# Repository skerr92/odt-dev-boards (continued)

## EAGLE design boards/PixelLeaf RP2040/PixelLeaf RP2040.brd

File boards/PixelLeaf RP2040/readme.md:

# PixelLeaf RP2040 Design Files

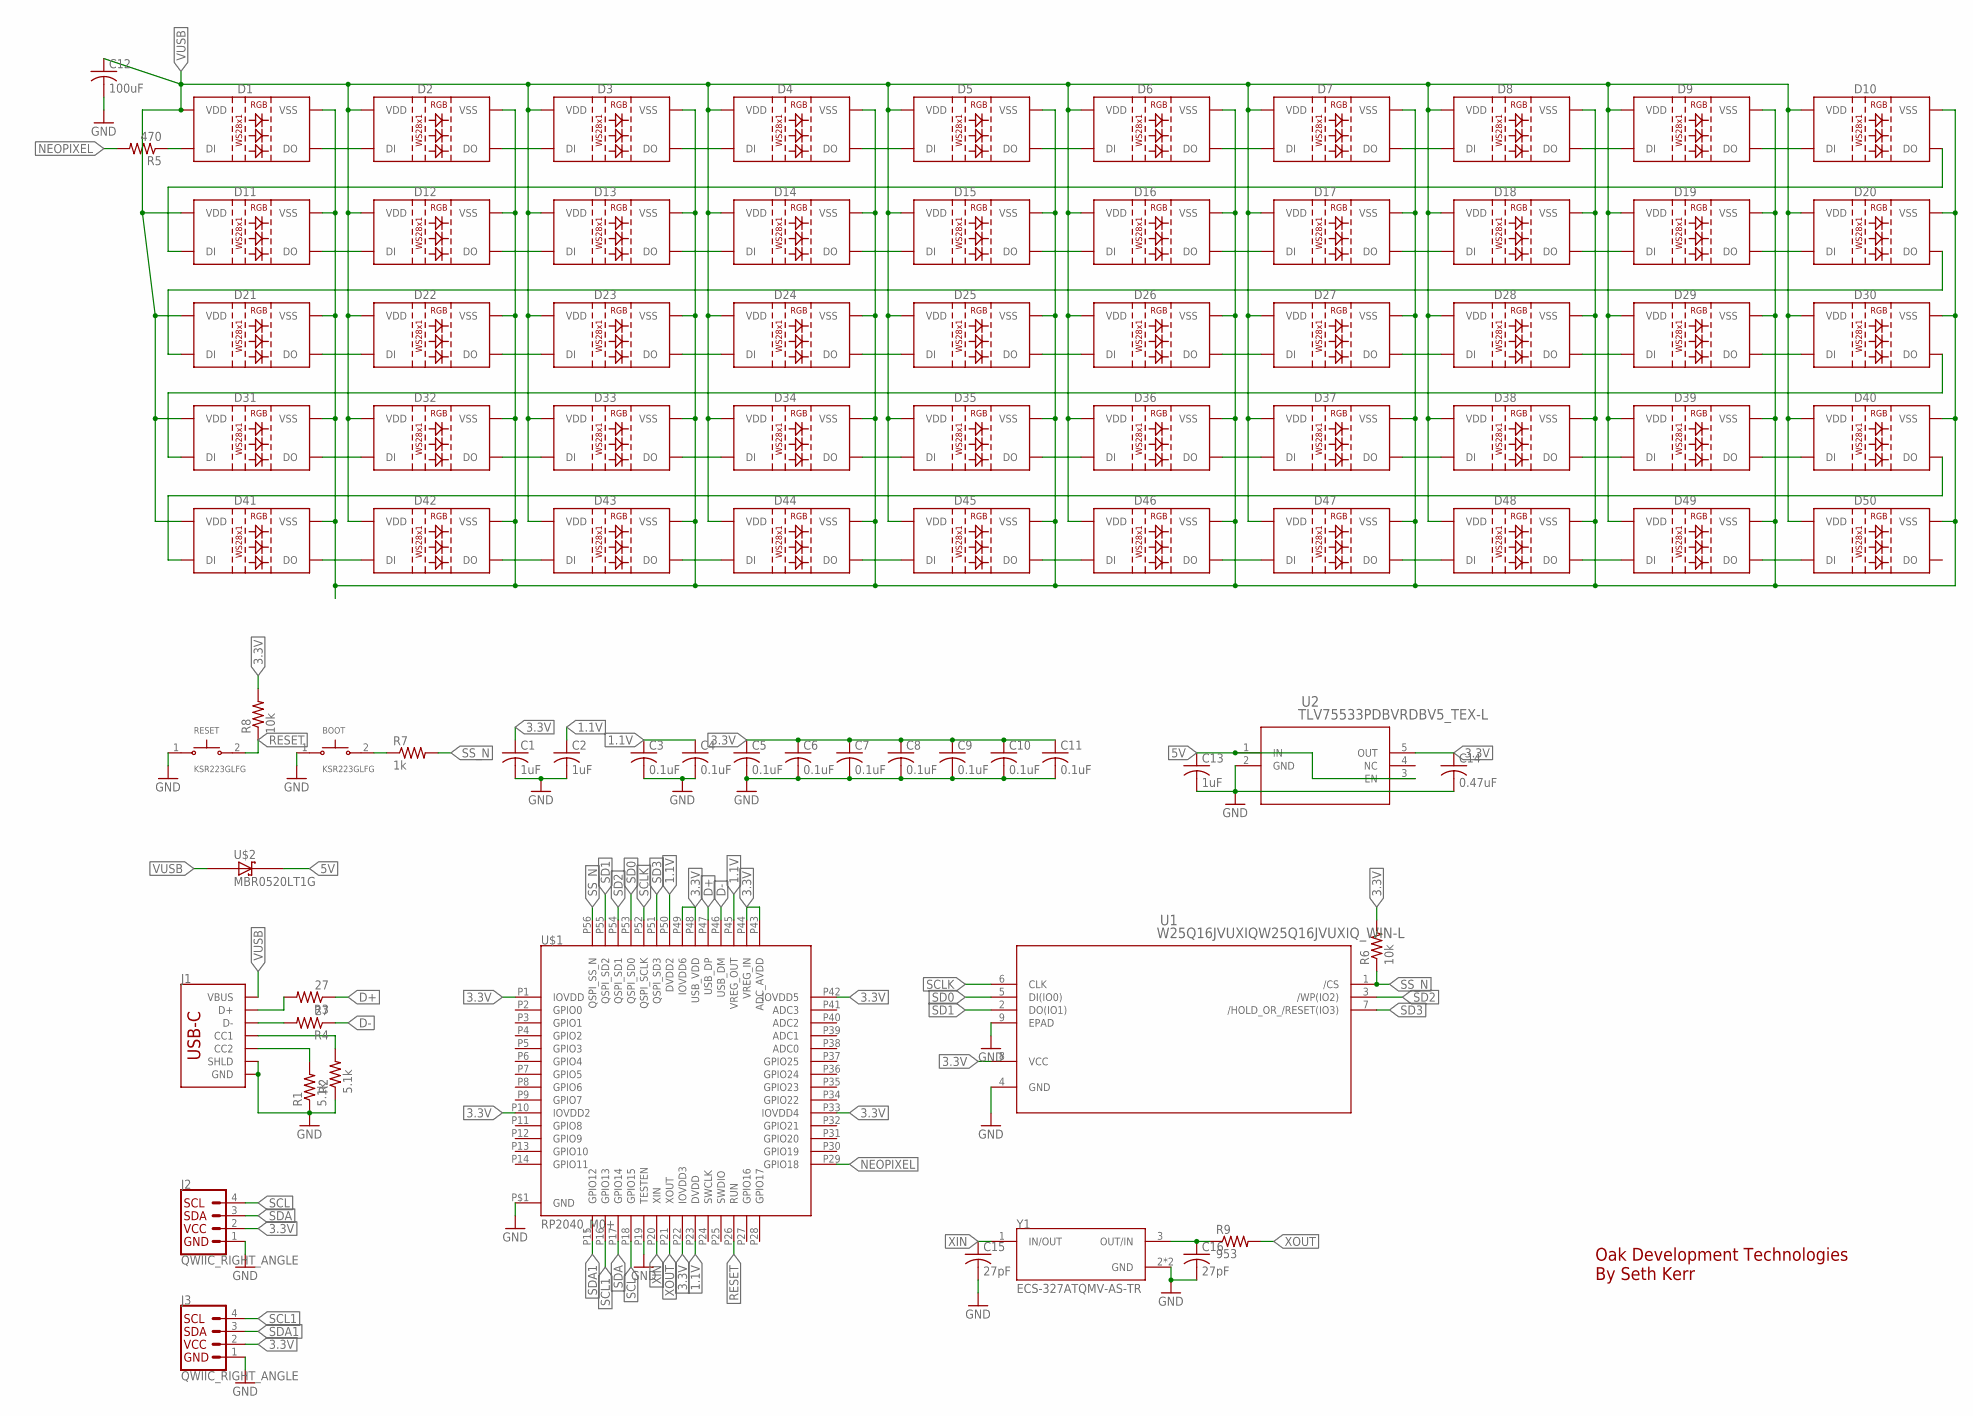
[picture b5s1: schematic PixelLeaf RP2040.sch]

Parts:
BOOT: KSR223GLFG; SW_KSR223GLFG
C1, C2, C13: 1uF; C0603
C3, C4, C5, C6, C7, C8, C9, C10, C11: 0.1uF; C0603
C12: 100uF; C1206
C14: 0.47uF; C0603
C15, C16: 27pF; C0402
D1, D2, D3, D4, D5, D6, D7, D8, D9, D10, D11, D12, D13, D14, D15, D16, D17, D18, D19, D20, D21, D22, D23, D24, D25, D26, D27, D28, D29, D30, D31, D32, D33, D34, D35, D36, D37, D38, D39, D40, D41, D42, D43, D44, D45, D46, D47, D48, D49, D50: WS2812BWS2812B-3535; WS2812-3535
J1: USB_C_2-LAYER_PADS; USB-C-16P-2LAYER-PADS
J2, J3: QWIIC_RIGHT_ANGLE; JST04_1MM_RA
R1, R2: 5.1k; R0603
R3, R4: 27; R0603
R5: 470; R0603
R6, R8: 10k; R0603
R7: 1k; R0603
R9: 953; R0402
RESET: KSR223GLFG; SW_KSR223GLFG
U1: W25Q16JVUXIQW25Q16JVUXIQ_WIN-L; W25Q16JVUXIQ_WIN-L
U2: TLV75533PDBVRDBV5_TEX-L; DBV5_TEX-L
U$1: RP2040_M0+; QFN-56
U$2: MBR0520LT1G; SOD3716X117(SOD-123)
Y1: ECS-327ATQMV-AS-TR; XTAL_ECS-327ATQMV-AS-TR

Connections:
1.1V: C2.1, C3.1, C4.1, U$1.P23 (DVDD), U$1.P45 (VREG_OUT), U$1.P50 (DVDD2)
3.3V: C1.1, C5.1, C6.1, C7.1, C8.1, C9.1, C10.1, C11.1, C14.1, J2.2, J3.2, R6.2, R8.2, U1.8 (VCC), U2.5 (OUT), U$1.P1 (IOVDD), U$1.P10 (IOVDD2), U$1.P22 (IOVDD3), U$1.P33 (IOVDD4), U$1.P42 (IOVDD5), U$1.P43 (ADC_AVDD), U$1.P44 (VREG_IN), U$1.P48 (USB_VDD), U$1.P49 (IOVDD6)
5V: C13.1, U2.1 (IN), U2.3 (EN), U$2.1 (C)
D+: R3.1, U$1.P47 (USB_DP)
D-: R4.1, U$1.P46 (USB_DM)
GND: BOOT.1, C1.2, C2.2, C3.2, C4.2, C5.2, C6.2, C7.2, C8.2, C9.2, C10.2, C11.2, C12.2, C13.2, C14.2, C15.2, C16.2, D1.VSS, D2.VSS, D3.VSS, D4.VSS, D5.VSS, D6.VSS, D7.VSS, D8.VSS, D9.VSS, D10.VSS, D11.VSS, D12.VSS, D13.VSS, D14.VSS, D15.VSS, D16.VSS, D17.VSS, D18.VSS, D19.VSS, D20.VSS, D21.VSS, D22.VSS, D23.VSS, D24.VSS, D25.VSS, D26.VSS, D27.VSS, D28.VSS, D29.VSS, D30.VSS, D31.VSS, D32.VSS, D33.VSS, D34.VSS, D35.VSS, D36.VSS, D37.VSS, D38.VSS, D39.VSS, D40.VSS, D41.VSS, D42.VSS, D43.VSS, D44.VSS, D45.VSS, D46.VSS, D47.VSS, D48.VSS, D49.VSS, D50.VSS, J1.GND, J1.GND2 (GND), J1.P$1 (SHLD), J1.P$2 (SHLD), J1.P$3 (SHLD), J1.P$4 (SHLD), J1.SHLD1 (SHLD), J1.SHLD2 (SHLD), J1.SHLD3 (SHLD), J1.SHLD4 (SHLD), J2.1, J3.1, R1.1, R2.1, RESET.1, U1.4 (GND), U1.9 (EPAD), U2.2 (GND), U$1.P19 (TESTEN), U$1.P$1 (GND), Y1.2 (GND), Y1.4 (GND)
unnamed: J1.A6 (D+), J1.B6 (D+), R3.2
unnamed: J1.A7 (D-), J1.B7 (D-), R4.2
unnamed: J1.A5 (CC1), R2.2
unnamed: J1.B5 (CC2), R1.2
unnamed: D1.DIN (DI), R5.1
unnamed: C16.1, R9.1, Y1.3 (OUT/IN)
unnamed: D41.DOUT (DO), D42.DIN (DI)
unnamed: D42.DOUT (DO), D43.DIN (DI)
unnamed: D43.DOUT (DO), D44.DIN (DI)
unnamed: D44.DOUT (DO), D45.DIN (DI)
unnamed: D45.DOUT (DO), D46.DIN (DI)
unnamed: D46.DOUT (DO), D47.DIN (DI)
unnamed: D47.DOUT (DO), D48.DIN (DI)
unnamed: D48.DOUT (DO), D49.DIN (DI)
unnamed: D49.DOUT (DO), D50.DIN (DI)
unnamed: D40.DOUT (DO), D41.DIN (DI)
unnamed: D31.DOUT (DO), D32.DIN (DI)
unnamed: D32.DOUT (DO), D33.DIN (DI)
unnamed: D33.DOUT (DO), D34.DIN (DI)
unnamed: D34.DOUT (DO), D35.DIN (DI)
unnamed: D35.DOUT (DO), D36.DIN (DI)
unnamed: D36.DOUT (DO), D37.DIN (DI)
unnamed: D37.DOUT (DO), D38.DIN (DI)
unnamed: D38.DOUT (DO), D39.DIN (DI)
unnamed: D39.DOUT (DO), D40.DIN (DI)
unnamed: D30.DOUT (DO), D31.DIN (DI)
unnamed: D21.DOUT (DO), D22.DIN (DI)
unnamed: D22.DOUT (DO), D23.DIN (DI)
unnamed: D23.DOUT (DO), D24.DIN (DI)
unnamed: D24.DOUT (DO), D25.DIN (DI)
unnamed: D25.DOUT (DO), D26.DIN (DI)
unnamed: D26.DOUT (DO), D27.DIN (DI)
unnamed: D27.DOUT (DO), D28.DIN (DI)
unnamed: D28.DOUT (DO), D29.DIN (DI)
unnamed: D29.DOUT (DO), D30.DIN (DI)
unnamed: D20.DOUT (DO), D21.DIN (DI)
unnamed: D11.DOUT (DO), D12.DIN (DI)
unnamed: D12.DOUT (DO), D13.DIN (DI)
unnamed: D13.DOUT (DO), D14.DIN (DI)
unnamed: D14.DOUT (DO), D15.DIN (DI)
unnamed: D15.DOUT (DO), D16.DIN (DI)
unnamed: D16.DOUT (DO), D17.DIN (DI)
unnamed: D17.DOUT (DO), D18.DIN (DI)
unnamed: D18.DOUT (DO), D19.DIN (DI)
unnamed: D19.DOUT (DO), D20.DIN (DI)
unnamed: D10.DOUT (DO), D11.DIN (DI)
unnamed: D1.DOUT (DO), D2.DIN (DI)
unnamed: D2.DOUT (DO), D3.DIN (DI)
unnamed: D3.DOUT (DO), D4.DIN (DI)
unnamed: D4.DOUT (DO), D5.DIN (DI)
unnamed: D5.DOUT (DO), D6.DIN (DI)
unnamed: D6.DOUT (DO), D7.DIN (DI)
unnamed: D7.DOUT (DO), D8.DIN (DI)
unnamed: D8.DOUT (DO), D9.DIN (DI)
unnamed: D9.DOUT (DO), D10.DIN (DI)
unnamed: BOOT.2, R7.1
NEOPIXEL: R5.2, U$1.P29 (GPIO18)
RESET: R8.1, RESET.2, U$1.P26 (RUN)
SCL: J2.4, U$1.P18 (GPIO15)
SCL1: J3.4, U$1.P16 (GPIO13)
SCLK: U1.6 (CLK), U$1.P52 (QSPI_SCLK)
SD0: U1.5 (DI(IO0)), U$1.P53 (QSPI_SD0)
SD1: U1.2 (DO(IO1)), U$1.P55 (QSPI_SD2)
SD2: U1.3 (/WP(IO2)), U$1.P54 (QSPI_SD1)
SD3: U1.7 (/HOLD_OR_/RESET(IO3)), U$1.P51 (QSPI_SD3)
SDA: J2.3, U$1.P17 (GPIO14)
SDA1: J3.3, U$1.P15 (GPIO12)
SS_N: R6.1, R7.2, U1.1 (/CS), U$1.P56 (QSPI_SS_N)
VUSB: C12.1, D1.VDD, D2.VDD, D3.VDD, D4.VDD, D5.VDD, D6.VDD, D7.VDD, D8.VDD, D9.VDD, D10.VDD, D11.VDD, D12.VDD, D13.VDD, D14.VDD, D15.VDD, D16.VDD, D17.VDD, D18.VDD, D19.VDD, D20.VDD, D21.VDD, D22.VDD, D23.VDD, D24.VDD, D25.VDD, D26.VDD, D27.VDD, D28.VDD, D29.VDD, D30.VDD, D31.VDD, D32.VDD, D33.VDD, D34.VDD, D35.VDD, D36.VDD, D37.VDD, D38.VDD, D39.VDD, D40.VDD, D41.VDD, D42.VDD, D43.VDD, D44.VDD, D45.VDD, D46.VDD, D47.VDD, D48.VDD, D49.VDD, D50.VDD, J1.VBUS1 (VBUS), J1.VBUS2 (VBUS), U$2.2 (A)
XIN: C15.1, U$1.P20 (XIN), Y1.1 (IN/OUT)
XOUT: R9.2, U$1.P21 (XOUT)

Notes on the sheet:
Oak Development Technologies By Seth Kerr

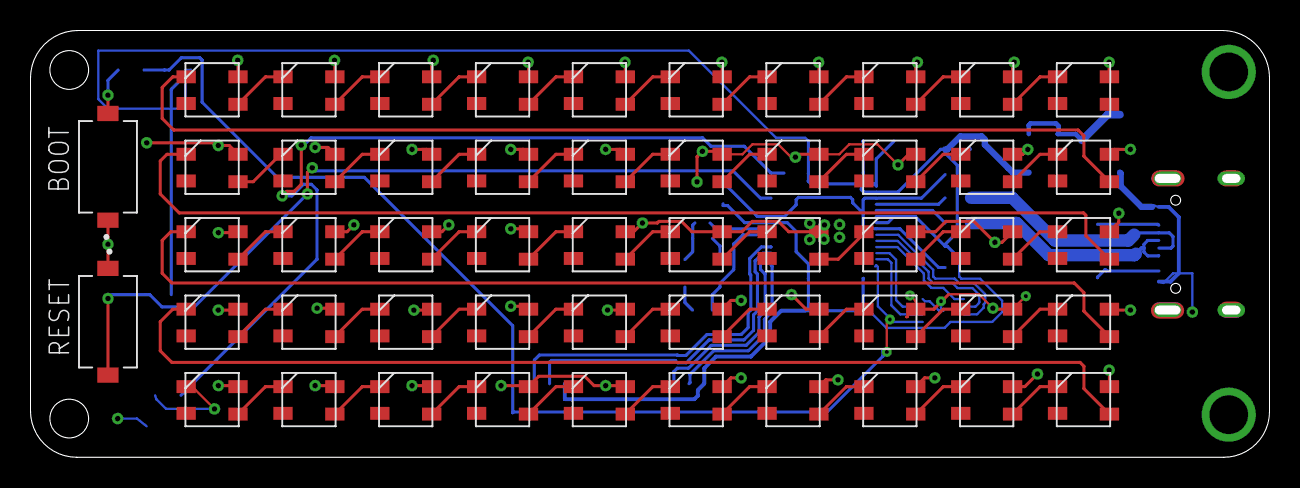
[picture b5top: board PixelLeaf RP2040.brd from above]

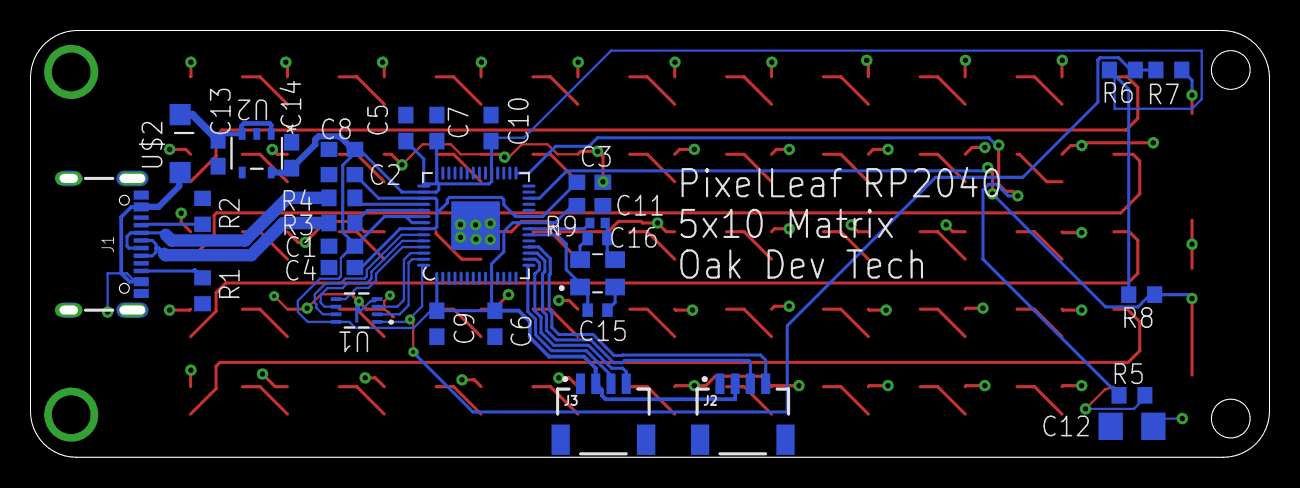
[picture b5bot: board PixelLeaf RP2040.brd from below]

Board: 2 copper layers, 81.3 x 28.0 mm, 85 parts (33 on the bottom side), 77 nets.

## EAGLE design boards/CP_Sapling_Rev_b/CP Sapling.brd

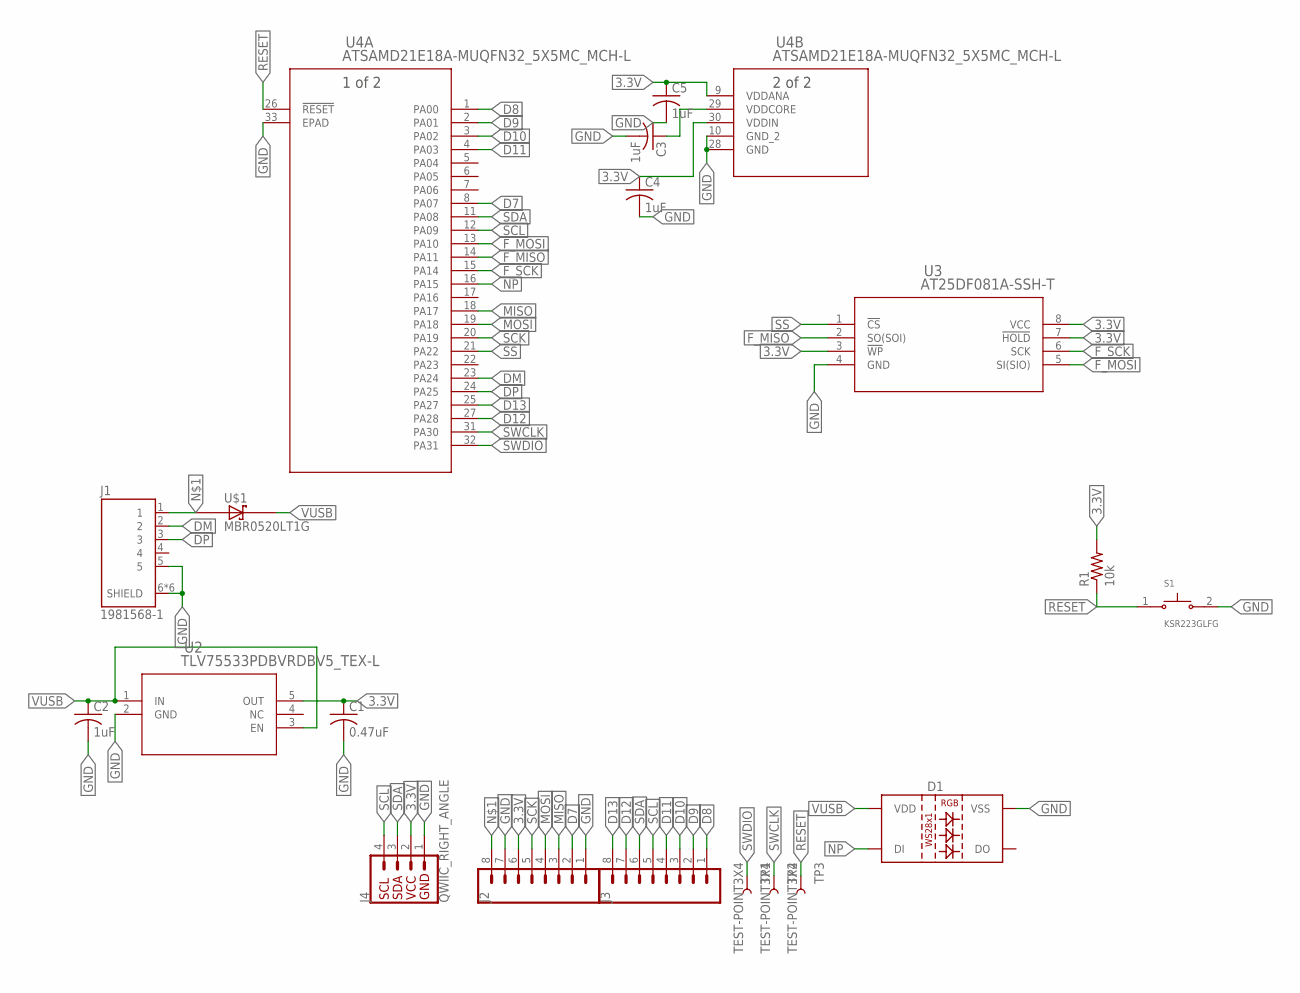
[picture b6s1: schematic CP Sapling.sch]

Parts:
C1: 0.47uF; C0402
C2, C3, C4, C5: 1uF; C0402
D1: WS2812B; WS2812-3535
J1: 1981568-1; TE_1981568-1
J2, J3: CONN_08NO_SILK_DNP; 1X08_NO_SILK
J4: QWIIC_RIGHT_ANGLE; JST04_1MM_RA
R1: 10k; R0402
S1: KSR223GLFG; SW_KSR223GLFG
TP1, TP2, TP3: TEST-POINT3X4; PAD.03X.04
U2: TLV75533PDBVRDBV5_TEX-L; DBV5_TEX-L
U3: AT25DF081A-SSH-T; SOIC_AT25DF081_ADO
U4: ATSAMD21E18A-MUQFN32_5X5MC_MCH-L; QFN32_5X5MC_MCH-L
U$1: MBR0520LT1G; SOD3716X117(SOD-123)

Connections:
3.3V: C1.1, C4.1, C5.1, J2.6, J4.2, R1.2, U2.5 (OUT), U3.3 (!WP), U3.7 (!HOLD), U3.8 (VCC), U4.9 (VDDANA), U4.30 (VDDIN)
D7: J2.2, U4.8 (PA07)
D8: J3.1, U4.1 (PA00)
D9: J3.2, U4.2 (PA01)
D10: J3.3, U4.3 (PA02)
D11: J3.4, U4.4 (PA03)
D12: J3.7, U4.27 (PA28)
D13: J3.8, U4.25 (PA27)
DM: J1.2, U4.23 (PA24)
DP: J1.3, U4.24 (PA25)
F_MISO: U3.2 (SO(SOI)), U4.14 (PA11)
F_MOSI: U3.5 (SI(SIO)), U4.13 (PA10)
F_SCK: U3.6 (SCK), U4.15 (PA14)
GND: C1.2, C2.2, C3.2, C4.2, C5.2, D1.VSS, J1.5, J1.6 (SHIELD), J1.7 (SHIELD), J1.8 (SHIELD), J1.9 (SHIELD), J1.10 (SHIELD), J1.11 (SHIELD), J2.1, J2.7, J4.1, S1.2, U2.2 (GND), U3.4 (GND), U4.10 (GND_2), U4.28 (GND), U4.33 (EPAD)
MISO: J2.3, U4.18 (PA17)
MOSI: J2.4, U4.19 (PA18)
unnamed: J1.1, J2.8, U$1.2 (A)
unnamed: C3.1, U4.29 (VDDCORE)
NP: D1.DIN (DI), U4.16 (PA15)
RESET: R1.1, S1.1, TP3.P$1, U4.26 (!RESET)
SCK: J2.5, U4.20 (PA19)
SCL: J3.5, J4.4, U4.12 (PA09)
SDA: J3.6, J4.3, U4.11 (PA08)
SS: U3.1 (!CS), U4.21 (PA22)
SWCLK: TP2.P$1, U4.31 (PA30)
SWDIO: TP1.P$1, U4.32 (PA31)
VUSB: C2.1, D1.VDD, U2.1 (IN), U2.3 (EN), U$1.1 (C)

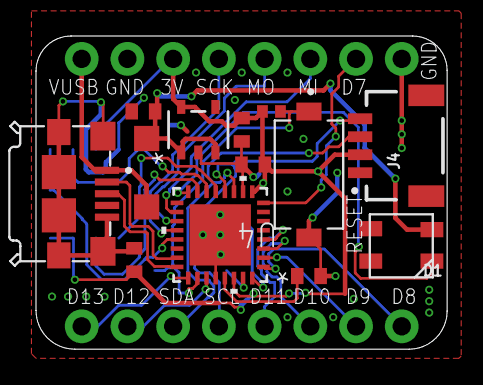
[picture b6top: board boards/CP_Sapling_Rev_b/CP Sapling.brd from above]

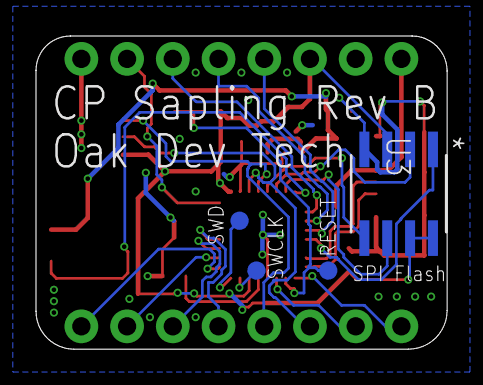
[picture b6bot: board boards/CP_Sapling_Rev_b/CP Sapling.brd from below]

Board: 2 copper layers, 22.8 x 17.4 mm, 19 parts (4 on the bottom side), 27 nets.

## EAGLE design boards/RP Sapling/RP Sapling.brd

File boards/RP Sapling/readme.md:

# repo for the RP Sapling files

This repo contains the Oak Development Technologies board files for the RP Sapling and the RP2040 Eagle CAD Library

# downloading the RP Sapling Eagle CAD Library
for Windows Users
```sh
cd ..\Eagle\libraries\
wget https://github.com/skerr92/odt-dev-boards/blob/master/boards/RP%20Sapling/RP2040_M0.lbr
```
for Mac Users
```sh
cd Eagle/libraries
wget https://github.com/skerr92/odt-dev-boards/blob/master/boards/RP%20Sapling/RP2040_M0.lbr
```
Alternatively, you can use curl

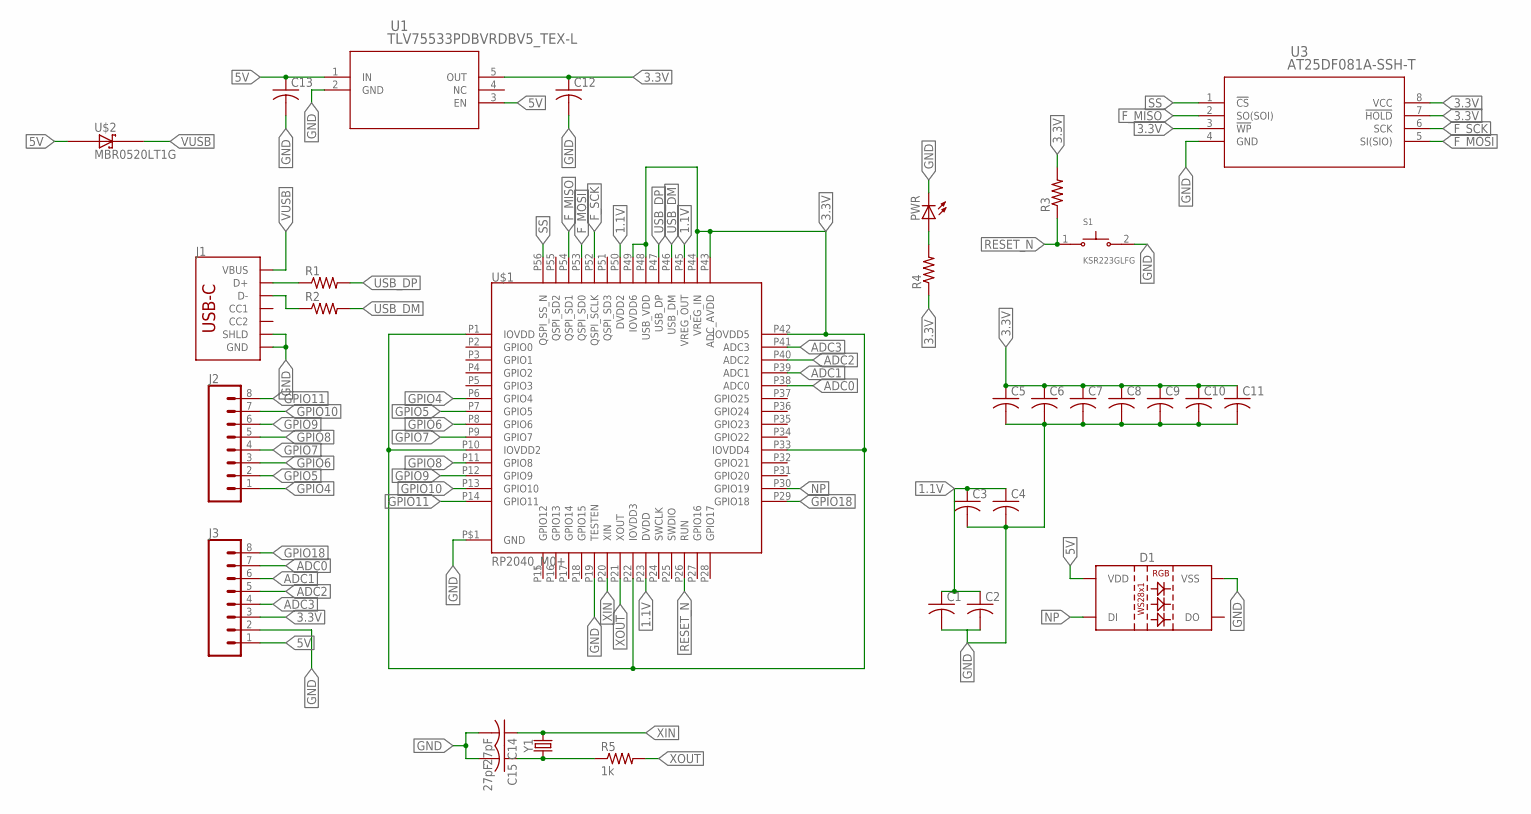
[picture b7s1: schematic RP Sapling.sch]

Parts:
C1, C2, C3, C4, C5, C6, C7, C8, C9, C10, C11, C12, C13: C-USC0402; C0402
C14, C15: 27pF; C0402
D1: WS2812BWS2812B-1515; WS2812B-1515
J1: USB_C_2-LAYER; USB-C-16P
J2, J3: CONN_08NO_SILK_DNP; 1X08_NO_SILK
PWR: LEDCHIPLED_0805; CHIPLED_0805
R1, R2, R4: R-US_R0603; R0603
R3: R-US_R0402; R0402
R5: 1k; R0402
S1: KSR223GLFG; SW_KSR223GLFG
U1: TLV75533PDBVRDBV5_TEX-L; DBV5_TEX-L
U3: AT25DF081A-SSH-T; SOIC_AT25DF081_ADO
U$1: RP2040_M0+; QFN-56
U$2: MBR0520LT1G; SOD3716X117(SOD-123)
Y1: CRYSTALSMD-5X3.2-2PAD; CRYSTAL-SMD-5X3.2-2PAD

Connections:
1.1V: C1.1, C2.1, C3.1, C4.1, U$1.P23 (DVDD), U$1.P45 (VREG_OUT), U$1.P50 (DVDD2)
3.3V: C5.1, C6.1, C7.1, C8.1, C9.1, C10.1, C11.1, C12.1, J3.3, R3.2, R4.1, U1.5 (OUT), U3.3 (!WP), U3.7 (!HOLD), U3.8 (VCC), U$1.P1 (IOVDD), U$1.P10 (IOVDD2), U$1.P22 (IOVDD3), U$1.P33 (IOVDD4), U$1.P42 (IOVDD5), U$1.P43 (ADC_AVDD), U$1.P44 (VREG_IN), U$1.P48 (USB_VDD), U$1.P49 (IOVDD6)
5V: C13.1, D1.VDD, J3.1, U1.1 (IN), U1.3 (EN), U$2.2 (A)
ADC0: J3.7, U$1.P38 (ADC0)
ADC1: J3.6, U$1.P39 (ADC1)
ADC2: J3.5, U$1.P40 (ADC2)
ADC3: J3.4, U$1.P41 (ADC3)
F_MISO: U3.2 (SO(SOI)), U$1.P54 (QSPI_SD1)
F_MOSI: U3.5 (SI(SIO)), U$1.P53 (QSPI_SD0)
F_SCK: U3.6 (SCK), U$1.P52 (QSPI_SCLK)
GND: C1.2, C2.2, C3.2, C4.2, C5.2, C6.2, C7.2, C8.2, C9.2, C10.2, C11.2, C12.2, C13.2, C14.2, C15.2, D1.GND (VSS), J1.GND, J1.GND2 (GND), J1.SHLD1 (SHLD), J1.SHLD2 (SHLD), J1.SHLD3 (SHLD), J1.SHLD4 (SHLD), J1.SHLD5 (SHLD), J1.SHLD6 (SHLD), J1.SHLD7 (SHLD), J1.SHLD8 (SHLD), J3.2, PWR.C, S1.2, U1.2 (GND), U3.4 (GND), U$1.P19 (TESTEN), U$1.P$1 (GND)
GPIO4: J2.1, U$1.P6 (GPIO4)
GPIO5: J2.2, U$1.P7 (GPIO5)
GPIO6: J2.3, U$1.P8 (GPIO6)
GPIO7: J2.4, U$1.P9 (GPIO7)
GPIO8: J2.5, U$1.P11 (GPIO8)
GPIO9: J2.6, U$1.P12 (GPIO9)
GPIO10: J2.7, U$1.P13 (GPIO10)
GPIO11: J2.8, U$1.P14 (GPIO11)
GPIO18: J3.8, U$1.P29 (GPIO18)
unnamed: PWR.A, R4.2
unnamed: C15.1, R5.1, Y1.P$1 (1)
unnamed: J1.A6 (D+), J1.B6 (D+), R1.1
unnamed: J1.A7 (D-), J1.B7 (D-), R2.1
NP: D1.DIN (DI), U$1.P30 (GPIO19)
RESET_N: R3.1, S1.1, U$1.P26 (RUN)
SS: U3.1 (!CS), U$1.P56 (QSPI_SS_N)
USB_DM: R2.2, U$1.P46 (USB_DM)
USB_DP: R1.2, U$1.P47 (USB_DP)
VUSB: J1.VBUS1 (VBUS), J1.VBUS2 (VBUS), U$2.1 (C)
XIN: C14.1, U$1.P20 (XIN), Y1.P$2 (2)
XOUT: R5.2, U$1.P21 (XOUT)

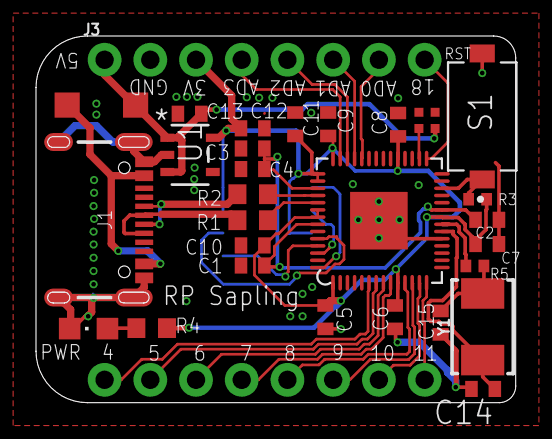
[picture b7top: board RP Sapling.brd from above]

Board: 2 copper layers, 26.6 x 20.4 mm, 31 parts (1 on the bottom side), 32 nets.

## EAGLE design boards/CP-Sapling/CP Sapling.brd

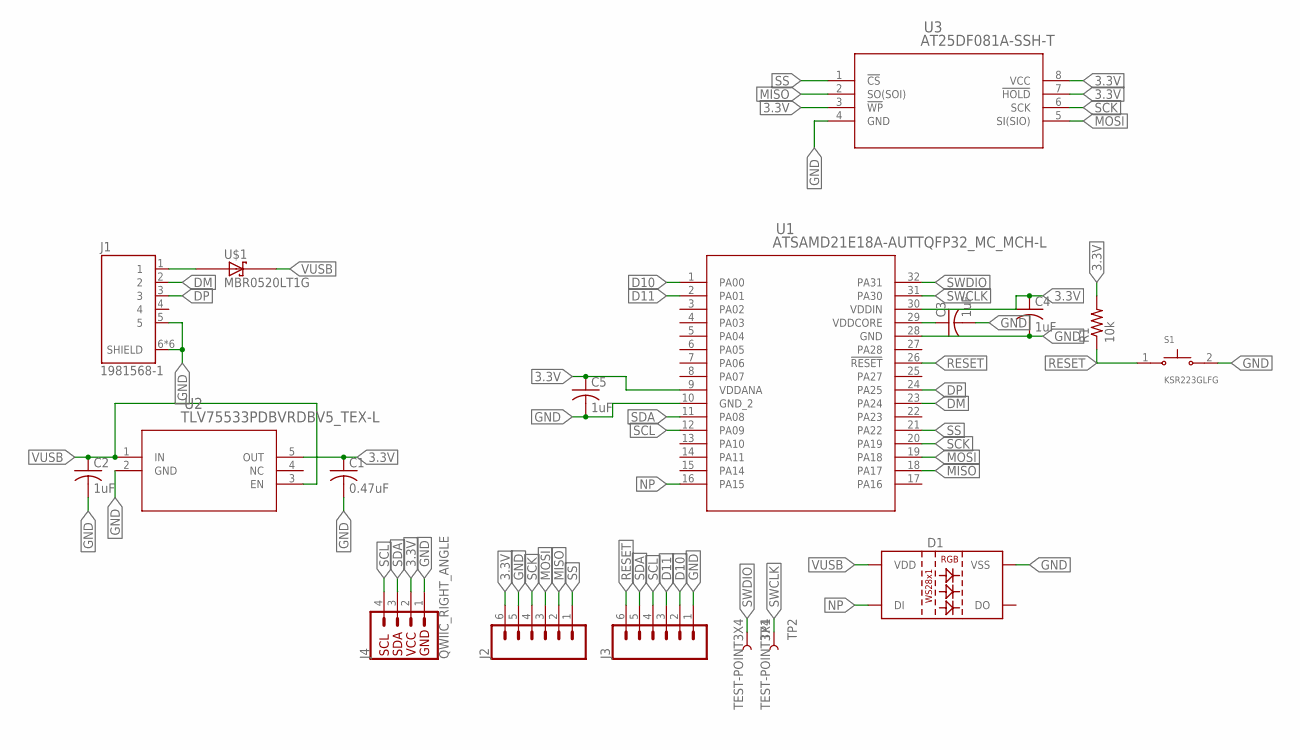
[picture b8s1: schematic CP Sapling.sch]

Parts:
C1: 0.47uF; C0402
C2, C3, C4, C5: 1uF; C0402
D1: WS2812B; WS2812B-3535
J1: 1981568-1; TE_1981568-1
J2, J3: CONN_06NO_SILK_NO_POP; 1X06_NO_SILK
J4: QWIIC_RIGHT_ANGLE; JST04_1MM_RA
R1: 10k; R0402
S1: KSR223GLFG; SW_KSR223GLFG
TP1, TP2: TEST-POINT3X4; PAD.03X.04
U1: ATSAMD21E18A-AUTTQFP32_MC_MCH-L; TQFP32_MC_MCH-L
U2: TLV75533PDBVRDBV5_TEX-L; DBV5_TEX-L
U3: AT25DF081A-SSH-T; SOIC_AT25DF081_ADO
U$1: MBR0520LT1G; SOD3716X117(SOD-123)

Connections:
3.3V: C1.1, C4.1, C5.1, J2.6, J4.2, R1.2, U1.9 (VDDANA), U1.30 (VDDIN), U2.5 (OUT), U3.3 (!WP), U3.7 (!HOLD), U3.8 (VCC)
D10: J3.2, U1.1 (PA00)
D11: J3.3, U1.2 (PA01)
DM: J1.2, U1.23 (PA24)
DP: J1.3, U1.24 (PA25)
GND: C1.2, C2.2, C3.2, C4.2, C5.2, D1.3 (VSS), J1.5, J1.6 (SHIELD), J1.7 (SHIELD), J1.8 (SHIELD), J1.9 (SHIELD), J1.10 (SHIELD), J1.11 (SHIELD), J2.5, J3.1, J4.1, S1.2, U1.10 (GND_2), U1.28 (GND), U2.2 (GND), U3.4 (GND)
MISO: J2.2, U1.18 (PA17), U3.2 (SO(SOI))
MOSI: J2.3, U1.19 (PA18), U3.5 (SI(SIO))
unnamed: J1.1, U$1.2 (A)
unnamed: C3.1, U1.29 (VDDCORE)
NP: D1.4 (DI), U1.16 (PA15)
RESET: J3.6, R1.1, S1.1, U1.26 (!RESET)
SCK: J2.4, U1.20 (PA19), U3.6 (SCK)
SCL: J3.4, J4.4, U1.12 (PA09)
SDA: J3.5, J4.3, U1.11 (PA08)
SS: J2.1, U1.21 (PA22), U3.1 (!CS)
SWCLK: TP2.P$1, U1.31 (PA30)
SWDIO: TP1.P$1, U1.32 (PA31)
VUSB: C2.1, D1.1 (VDD), U2.1 (IN), U2.3 (EN), U$1.1 (C)

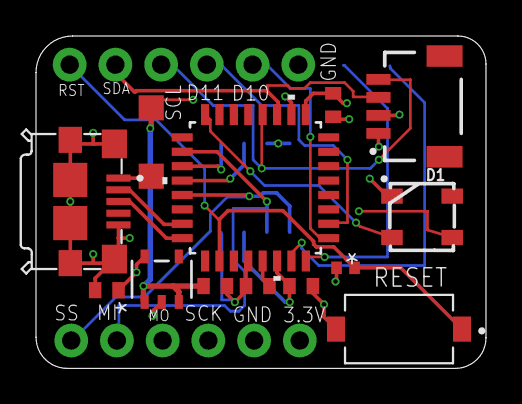
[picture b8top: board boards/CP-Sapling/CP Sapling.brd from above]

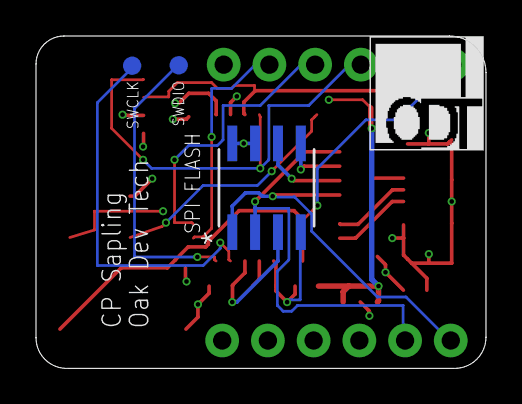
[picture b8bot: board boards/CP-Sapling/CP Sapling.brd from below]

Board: 4 copper layers, 25.0 x 18.5 mm, 18 parts (3 on the bottom side), 19 nets.

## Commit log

2020-09-15 Create board.mk
    adding board.mk file for CP-Sapling
2020-09-15 Create board_config.h
    adding the board configuration header file
2020-09-15 Add files via upload
    Adding applying boards and schematics
2020-09-17 Update LICENSE
    adding appropriate MIT License
2020-10-17 Add files via upload
    updating board and schematic files
2021-01-26 Add files via upload
    adding files for rp sapling
2021-01-30 adding instructions for getting eagle library
    used for getting eagle library files for RP2040 footprint
2021-04-27 folder for CP Sapling Rev B files
2021-04-27 cp sapling rev b stuff
2021-08-15 Add PixelWing Directory
2021-08-15 adding board and schematic files
2021-09-16 Update flash_pixelwing
2021-11-21 Add files via upload
    adding design files
